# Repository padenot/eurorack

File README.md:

# eurorack
eurorack modules hardware design files and associated material

- *.fpd : [Front Panel Designer](https://www.schaeffer-ag.de/en/downloads/front_panel_designer/)
- *.brd, *.sch : [Eagle](https://www.autodesk.com/products/eagle/overview)
- *.svg : [Inkscape](https://inkscape.org/en/)

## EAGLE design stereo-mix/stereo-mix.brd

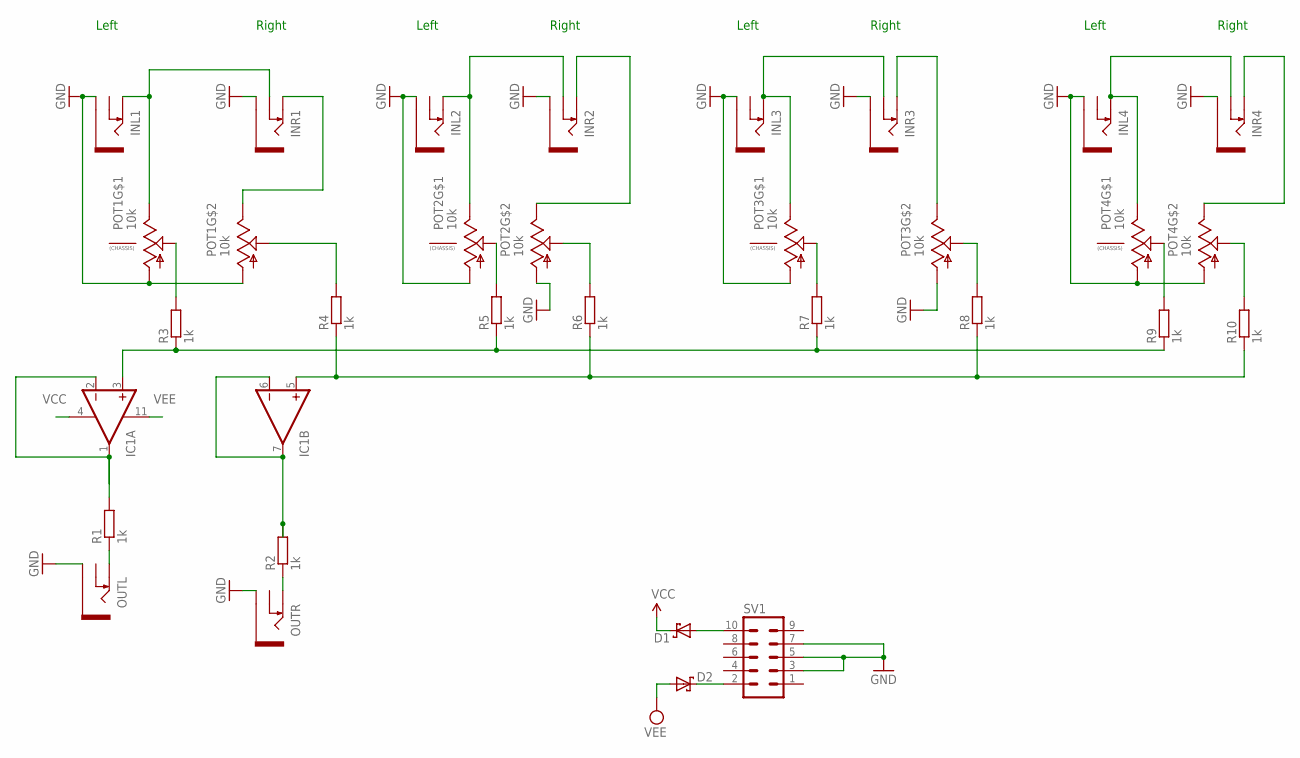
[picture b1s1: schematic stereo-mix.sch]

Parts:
D1, D2: 1N5819-B; DO41-7.6
IC1: LM324N; DIL14
INL1, INL2, INL3, INL4: THONKICONNNEW; WQP-PJ301M-12_JACK
INR1, INR2, INR3, INR4: THONKICONNNEW; WQP-PJ301M-12_JACK
OUTL: THONKICONNNEW; WQP-PJ301M-12_JACK
OUTR: THONKICONNNEW; WQP-PJ301M-12_JACK
POT1, POT2, POT3, POT4: 10k; DUAL_9MM_SNAP-IN_POT
R1, R2, R3, R4, R5, R6, R7, R8, R9, R10: 1k; 7MM_RESISTOR
SV1: EURO_POWER_HEADERREGULAR; EURO_POWER_HEADER

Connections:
GND: INL1.P$3_SLEEVE (SLEEVE), INL2.P$3_SLEEVE (SLEEVE), INL3.P$3_SLEEVE (SLEEVE), INL4.P$3_SLEEVE (SLEEVE), INR1.P$3_SLEEVE (SLEEVE), INR2.P$3_SLEEVE (SLEEVE), INR3.P$3_SLEEVE (SLEEVE), INR4.P$3_SLEEVE (SLEEVE), OUTL.P$3_SLEEVE (SLEEVE), OUTR.P$3_SLEEVE (SLEEVE), POT1.1 (A), POT1.1B (A), POT2.1 (A), POT2.1B (A), POT3.1 (A), POT3.1B (A), POT4.1 (A), POT4.1B (A), SV1.3, SV1.5, SV1.7
unnamed: POT1.2B (S), R4.2
unnamed: POT1.2 (S), R3.2
unnamed: POT2.2 (S), R5.2
unnamed: POT2.2B (S), R6.2
unnamed: POT3.2 (S), R7.2
unnamed: OUTL.P$1_TIP (TIP), R1.1
unnamed: POT3.2B (S), R8.2
unnamed: POT4.2 (S), R9.2
unnamed: POT4.2B (S), R10.2
unnamed: D2.C, SV1.2
unnamed: INR1.P$1_TIP (TIP), POT1.3B (E)
unnamed: INL2.P$1_TIP (TIP), INR2.P$2_SWITCH (SWITCH), POT2.3 (E)
unnamed: INR2.P$1_TIP (TIP), POT2.3B (E)
unnamed: D1.A, SV1.10
unnamed: INR3.P$1_TIP (TIP), POT3.3B (E)
unnamed: INR4.P$1_TIP (TIP), POT4.3B (E)
unnamed: OUTR.P$1_TIP (TIP), R2.1
unnamed: INL1.P$1_TIP (TIP), INR1.P$2_SWITCH (SWITCH), POT1.3 (E)
unnamed: IC1.6 (-IN), IC1.7 (OUT), R2.2
unnamed: IC1.1 (OUT), IC1.2 (-IN), R1.2
unnamed: INL3.P$1_TIP (TIP), INR3.P$2_SWITCH (SWITCH), POT3.3 (E)
unnamed: INL4.P$1_TIP (TIP), INR4.P$2_SWITCH (SWITCH), POT4.3 (E)
unnamed: IC1.3 (+IN), R3.1, R5.1, R7.1, R9.1
unnamed: IC1.5 (+IN), R4.1, R6.1, R8.1, R10.1
VCC: D1.C, IC1.4 (V+)
VEE: D2.A, IC1.11 (V-)

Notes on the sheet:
Left
Right

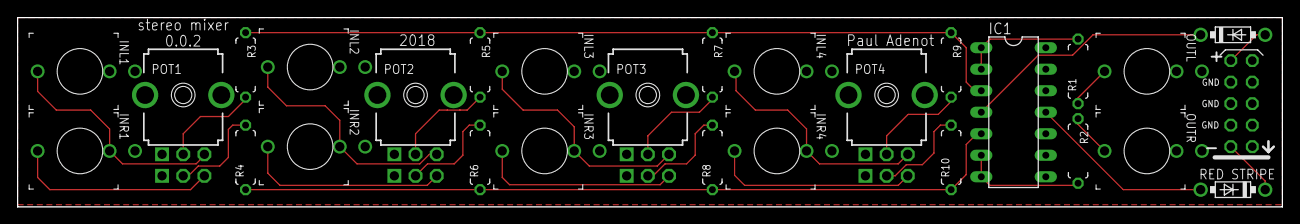
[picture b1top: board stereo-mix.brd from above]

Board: 2 copper layers, 149.4 x 22.4 mm, 28 parts (0 on the bottom side), 27 nets.

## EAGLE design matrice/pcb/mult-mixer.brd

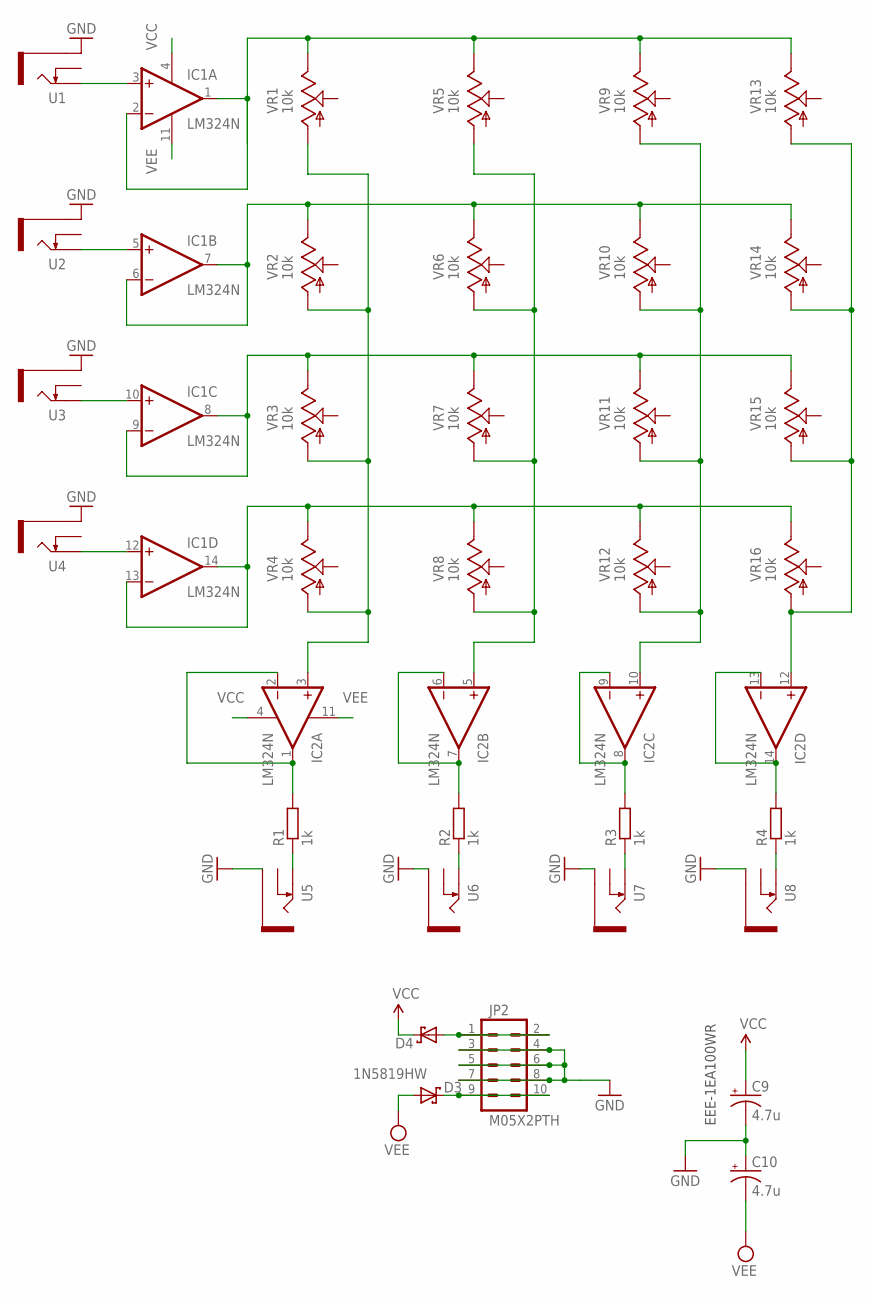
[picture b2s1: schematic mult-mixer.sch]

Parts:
C9, C10: 4.7u; PANASONIC_A
D3, D4: 1N5819HW; DO41-7.6
IC1, IC2: LM324N; DIL14
JP2: M05X2PTH; AVR_ICSP
R1, R2, R3, R4: 1k; 10MM_RESISTOR
U1, U2, U3, U4, U5, U6, U7, U8: THONKICONNNEW; WQP-PJ301M-12_JACK
VR1, VR2, VR3, VR4, VR5, VR6, VR7, VR8, VR9, VR10, VR11, VR12, VR13, VR14, VR15, VR16: 10k; 9MM_SNAP-IN_POT

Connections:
GND: C9.-, C10.+, JP2.3, JP2.4, JP2.5, JP2.6, JP2.7, JP2.8, U1.P$3_SLEEVE (SLEEVE), U2.P$3_SLEEVE (SLEEVE), U3.P$3_SLEEVE (SLEEVE), U4.P$3_SLEEVE (SLEEVE), U5.P$3_SLEEVE (SLEEVE), U6.P$3_SLEEVE (SLEEVE), U7.P$3_SLEEVE (SLEEVE), U8.P$3_SLEEVE (SLEEVE)
unnamed: IC1.3 (+IN), U1.P$1_TIP (TIP)
unnamed: IC1.1 (OUT), IC1.2 (-IN), VR1.3 (E), VR5.3 (E), VR9.3 (E), VR13.3 (E)
unnamed: IC1.5 (+IN), U2.P$1_TIP (TIP)
unnamed: IC1.10 (+IN), U3.P$1_TIP (TIP)
unnamed: IC1.12 (+IN), U4.P$1_TIP (TIP)
unnamed: IC1.6 (-IN), IC1.7 (OUT), VR2.3 (E), VR6.3 (E), VR10.3 (E), VR14.3 (E)
unnamed: IC2.3 (+IN), VR1.1 (A), VR2.1 (A), VR3.1 (A), VR4.1 (A)
unnamed: IC2.1 (OUT), IC2.2 (-IN), R1.2
unnamed: IC1.8 (OUT), IC1.9 (-IN), VR3.3 (E), VR7.3 (E), VR11.3 (E), VR15.3 (E)
unnamed: IC1.13 (-IN), IC1.14 (OUT), VR4.3 (E), VR8.3 (E), VR12.3 (E), VR16.3 (E)
unnamed: IC2.5 (+IN), VR5.1 (A), VR6.1 (A), VR7.1 (A), VR8.1 (A)
unnamed: IC2.6 (-IN), IC2.7 (OUT), R2.2
unnamed: IC2.10 (+IN), VR9.1 (A), VR10.1 (A), VR11.1 (A), VR12.1 (A)
unnamed: IC2.8 (OUT), IC2.9 (-IN), R3.2
unnamed: IC2.12 (+IN), VR13.1 (A), VR14.1 (A), VR15.1 (A), VR16.1 (A)
unnamed: IC2.13 (-IN), IC2.14 (OUT), R4.2
unnamed: R1.1, U5.P$1_TIP (TIP)
unnamed: R2.1, U6.P$1_TIP (TIP)
unnamed: R3.1, U7.P$1_TIP (TIP)
unnamed: R4.1, U8.P$1_TIP (TIP)
unnamed: D4.A, JP2.1, JP2.2
unnamed: D3.C, JP2.9, JP2.10
VCC: C9.+, D4.C, IC1.4 (V+), IC2.4 (V+)
VEE: C10.-, D3.A, IC1.11 (V-), IC2.11 (V-)

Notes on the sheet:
EEE-1EA100WR

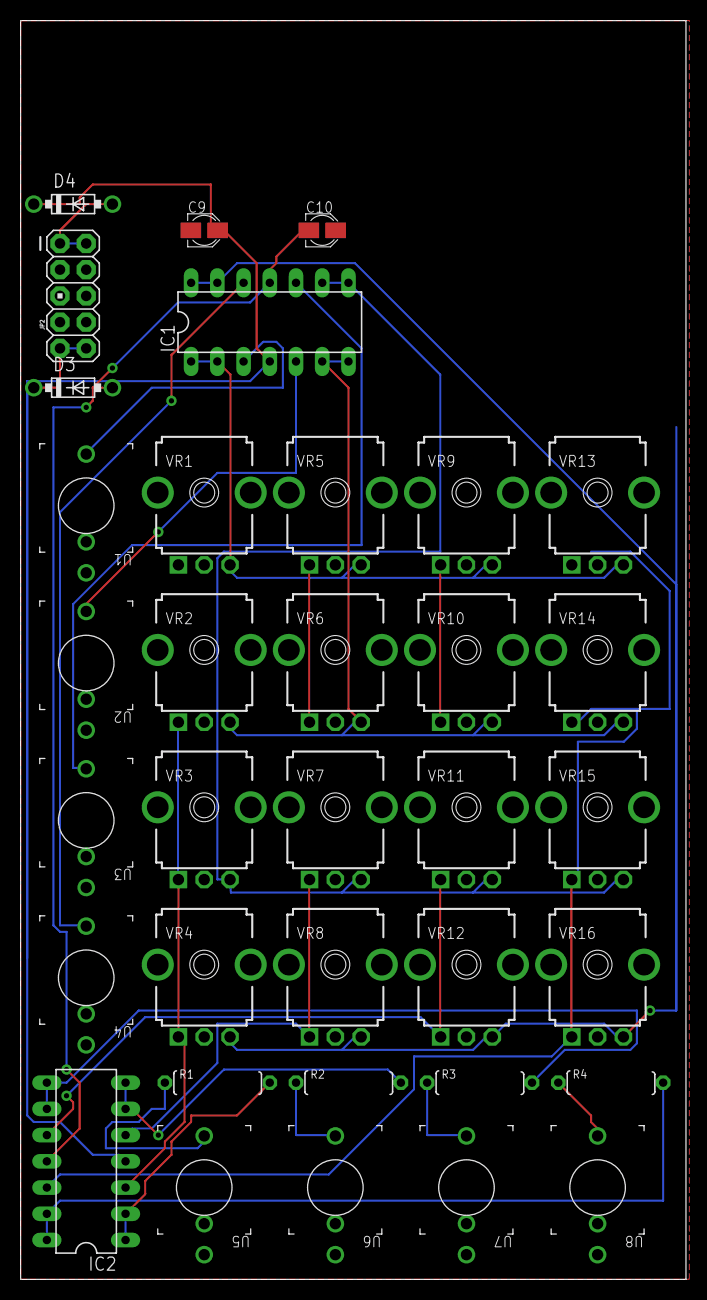
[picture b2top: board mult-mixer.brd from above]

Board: 2 copper layers, 64.4 x 121.9 mm, 35 parts (0 on the bottom side), 25 nets.

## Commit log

2018-09-06 resync desktop
2018-09-16 mult-mixer
2018-09-28 update with stereo mixer
2018-10-21 gerber
2018-11-19 DS_Store
2019-06-05 beginning matrix mixer / switch to kicad
2019-06-06 matrix 0.0.1
2019-11-17 beginning sequencer
2019-11-17 version sent to fab
2019-11-17 dunno
2019-11-17 svg 1U intellijel routing done, not sure about horizontal footprint of PCB
2020-01-12 matrix 0.0.2 but not routed
2020-01-18 matrix mixer 0.0.2 routed ready to send
2021-05-24 faceplate template matrix mixer
2021-05-25 matrix mixer: svg face plate at scale + re-save board file
2021-05-25 stereo mix front panel: new face plate with centering holes
